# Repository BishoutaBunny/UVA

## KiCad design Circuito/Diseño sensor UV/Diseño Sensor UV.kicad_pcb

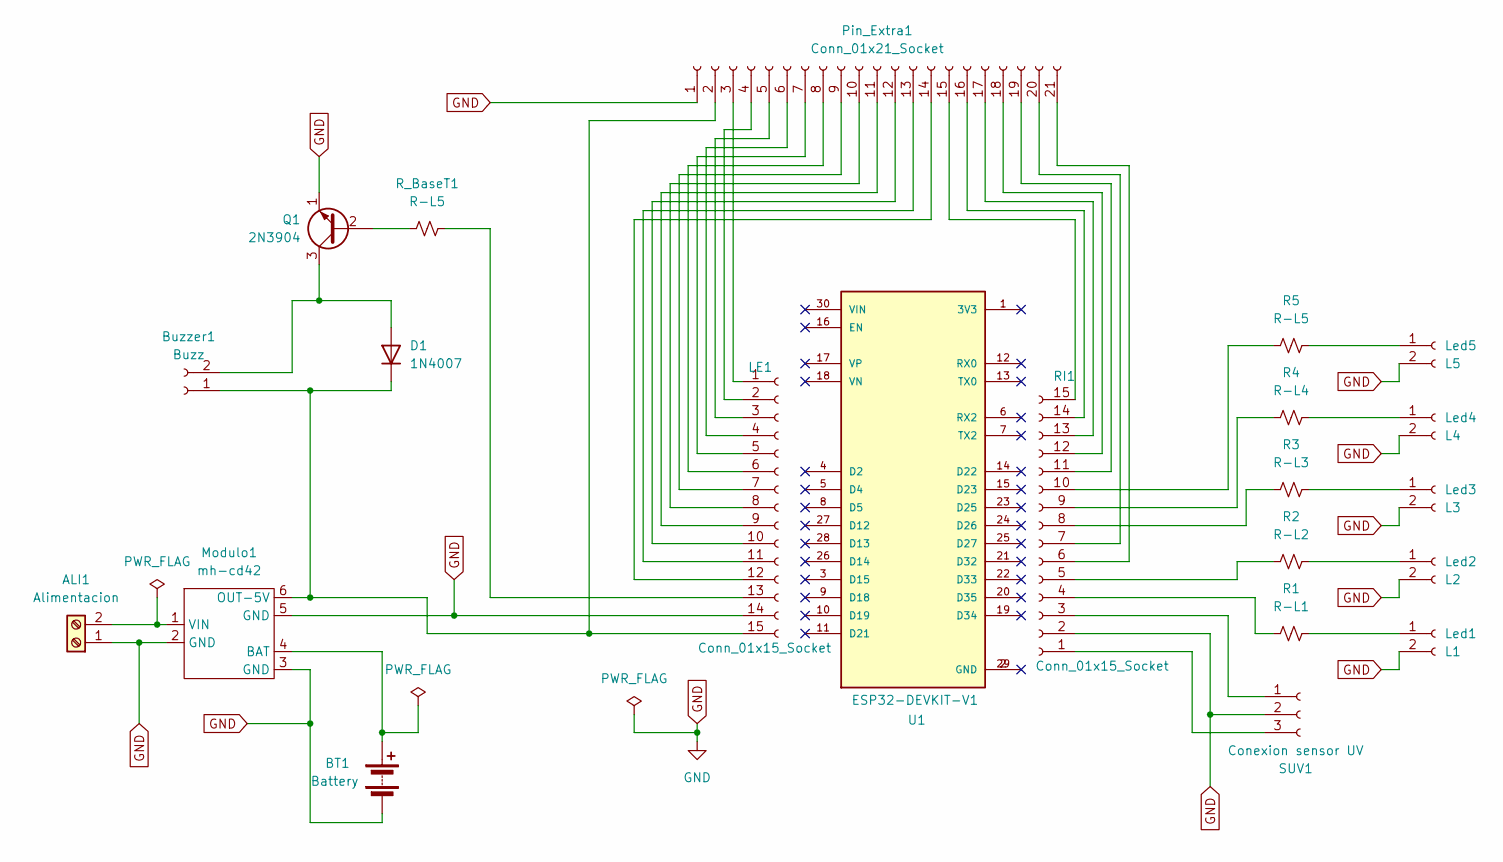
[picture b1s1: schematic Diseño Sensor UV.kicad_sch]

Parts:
ALI1: Alimentacion; TerminalBlock_RND_205-00287_1x02_P5.08mm_Horizontal
BT1: Battery; BatteryHolder_Keystone_1042_1x18650
Buzzer1: Buzz; PinSocket_1x02_P2.54mm_Vertical
D1: 1N4007; D_DO-41_SOD81_P10.16mm_Horizontal
LE1: Conn_01x15_Socket; PinSocket_1x15_P2.54mm_Vertical
Led1: L1; PinSocket_1x02_P2.54mm_Vertical
Led2: L2; PinSocket_1x02_P2.54mm_Vertical
Led3: L3; PinSocket_1x02_P2.54mm_Vertical
Led4: L4; PinSocket_1x02_P2.54mm_Vertical
Led5: L5; PinSocket_1x02_P2.54mm_Vertical
Modulo1: mh-cd42
Pin_Extra1: Conn_01x21_Socket; PinSocket_1x21_P2.54mm_Vertical
Q1: 2N3904; TO-92_Inline
R1: R-L1; R_Axial_DIN0207_L6.3mm_D2.5mm_P10.16mm_Horizontal
R2: R-L2; R_Axial_DIN0207_L6.3mm_D2.5mm_P10.16mm_Horizontal
R3: R-L3; R_Axial_DIN0207_L6.3mm_D2.5mm_P10.16mm_Horizontal
R4: R-L4; R_Axial_DIN0207_L6.3mm_D2.5mm_P10.16mm_Horizontal
R5: R-L5; R_Axial_DIN0207_L6.3mm_D2.5mm_P10.16mm_Horizontal
RI1: Conn_01x15_Socket; PinSocket_1x15_P2.54mm_Vertical
R_BaseT1: R-L5; R_Axial_DIN0207_L6.3mm_D2.5mm_P10.16mm_Horizontal
SUV1: Conexion sensor UV; PinSocket_1x03_P2.54mm_Vertical
U1: ESP32-DEVKIT-V1; MODULE_ESP32_DEVKIT_V1; PARTREV N/A

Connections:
GND: ALI1.1, BT1.2 (-), LE1.14, Led1.2, Led2.2, Led3.2, Led4.2, Led5.2, Modulo1.2 (GND), Modulo1.3 (GND), Modulo1.5 (GND), Pin_Extra1.1, Q1.1 (E), RI1.2, SUV1.2
unnamed: ALI1.2, Modulo1.1 (VIN)
unnamed: BT1.1 (+), Modulo1.4 (BAT)
unnamed: Buzzer1.1, D1.1 (K), LE1.15, Modulo1.6 (OUT-5V), Pin_Extra1.2
unnamed: Buzzer1.2, D1.2 (A), Q1.3 (C)
unnamed: LE1.1, Pin_Extra1.3
unnamed: LE1.2, Pin_Extra1.4
unnamed: LE1.3, Pin_Extra1.5
unnamed: LE1.4, Pin_Extra1.6
unnamed: LE1.5, Pin_Extra1.7
unnamed: LE1.6, Pin_Extra1.8
unnamed: LE1.7, Pin_Extra1.9
unnamed: LE1.8, Pin_Extra1.10
unnamed: LE1.9, Pin_Extra1.11
unnamed: LE1.10, Pin_Extra1.12
unnamed: LE1.11, Pin_Extra1.13
unnamed: LE1.12, Pin_Extra1.14
unnamed: LE1.13, R_BaseT1.2
unnamed: Led1.1, R1.2
unnamed: Led2.1, R2.2
unnamed: Led3.1, R3.2
unnamed: Led4.1, R4.2
unnamed: Led5.1, R5.2
unnamed: Pin_Extra1.15, RI1.15
unnamed: Pin_Extra1.16, RI1.14
unnamed: Pin_Extra1.17, RI1.13
unnamed: Pin_Extra1.18, RI1.12
unnamed: Pin_Extra1.19, RI1.11
unnamed: Pin_Extra1.20, RI1.7
unnamed: Pin_Extra1.21, RI1.6
unnamed: Q1.2 (B), R_BaseT1.1
unnamed: RI1.1, SUV1.3
unnamed: RI1.3, SUV1.1
unnamed: R1.1, RI1.4
unnamed: R2.1, RI1.5
unnamed: R3.1, RI1.8
unnamed: R4.1, RI1.9
unnamed: R5.1, RI1.10
unnamed: U1.2 (GND), U1.29 (GND)

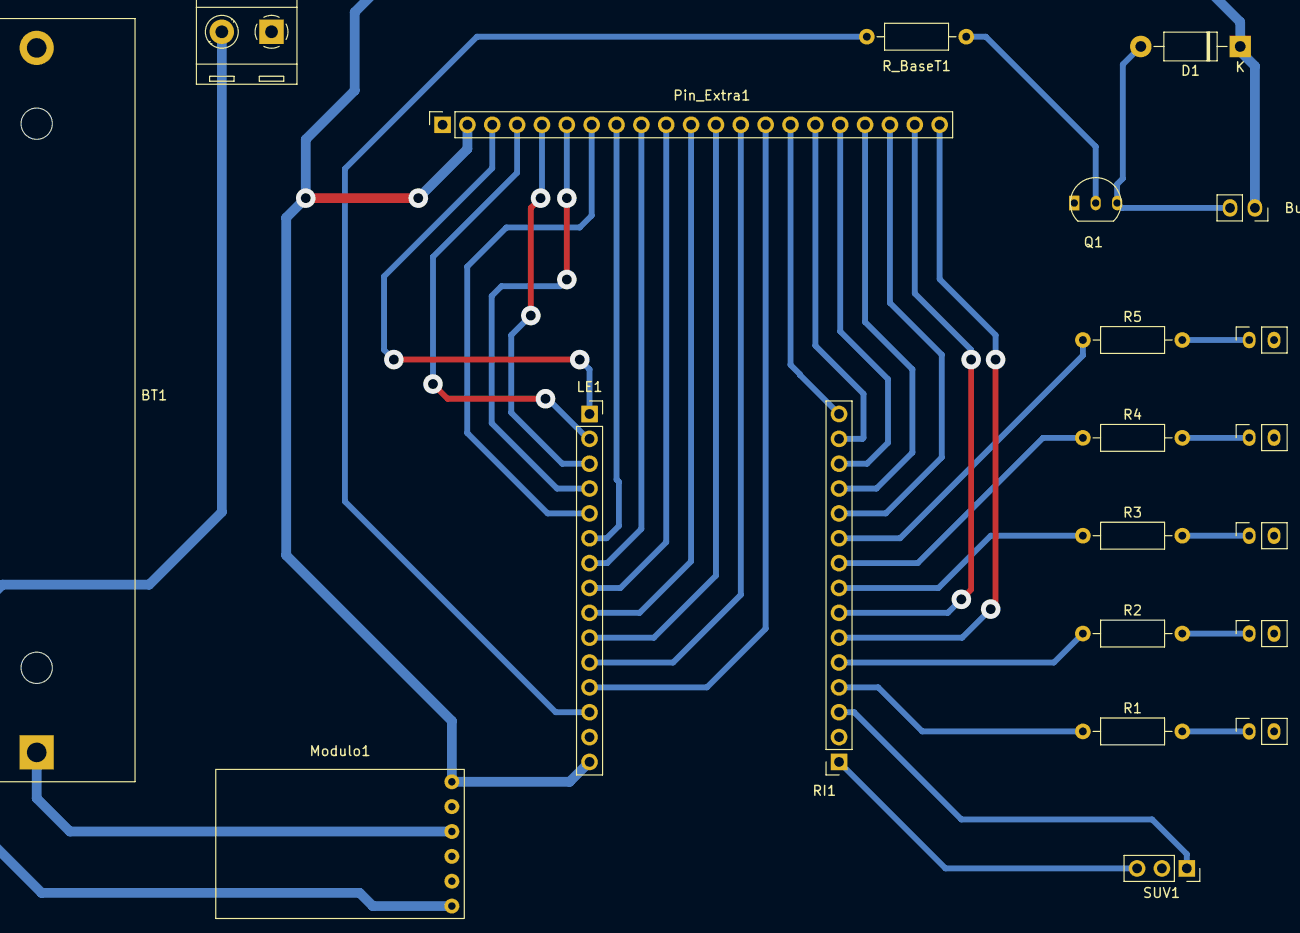
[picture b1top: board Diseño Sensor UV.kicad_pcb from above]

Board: 2 copper layers, 21 parts (0 on the bottom side), 38 nets.

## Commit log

2025-03-04 Create Carpetas
2025-03-04 Anexo carpetas
2025-03-04 Pagina web
    github de batiisaac
2025-03-04 Rename Funcionamiento _pycache_ to Funcionamiento de pycache
2025-03-04 Rename requirements.txt to requerimientos.txt
2025-03-08 Create Diseño sensor UV
